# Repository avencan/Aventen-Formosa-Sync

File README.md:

<div align="center">

> ## ⚠️ This board has been superseded
> **Aventen Formosa Sync** has been replaced by the **[Aventen Kypros](https://github.com/avencan/Aventen-Kypros)** — a completely redesigned board with WiFi 6, HDMI output, Gigabit Ethernet, native Zigbee/Thread/Matter, on-board audio codec, and 2× the compute power.
>
> 👉 **[See the Kypros → github.com/avencan/Aventen-Kypros](https://github.com/avencan/Aventen-Kypros)**
> 👉 **[Join the waitlist → aventeninnovations.com](https://aventeninnovations.com/#waitlist)**

</div>

---

<div align="center">

# Aventen Formosa Sync

### The board that started it all.

</div>

---

## Introduction

The Aventen Formosa Sync was Aventen's first development board — a high-performance board equipped with a 600MHz RT1060 MCU (overclockable to 1GHz under the right conditions), built-in WiFi 5 + Bluetooth with audio, USB OTG, RGB LEDs, USB-C connectivity, and comprehensive battery management.

Designed for IoT makers, professionals, and industrial solutions — it offered a compact, breadboardable form factor with serious performance.

---

## Specs

| Feature | Detail |
|---|---|
| **MCU** | NXP MIMXRT106SDVL6B — ARM Cortex-M7 @ 600MHz (overclockable to 1GHz) |
| **PSRAM** | 8MB |
| **Flash** | 16MB |
| **WiFi** | WiFi 5 — Murata Type 1ZM |
| **Bluetooth** | BT 5.0 |
| **SD Card** | Built-in MicroSD slot |
| **USB** | USB-C |
| **Ethernet** | 10/100 via LAN8720A |
| **LEDs** | RGB + status LED |
| **GPIO** | 35 header pins |
| **Debug** | SWD/JTAG |
| **Power** | Battery (JST) + USB-C LiPo charging |
| **Extras** | Chip antenna + IPX U.FL · Aux LDO 1A · RF switch |

---

## Add-on Boards

**RJ45 LAN8720A Ethernet Board:**
[github.com/avencan/Aventen-Formosa-Sync/tree/main/RJ45](https://github.com/avencan/Aventen-Formosa-Sync/tree/main/RJ45)

---

## Status

Formosa Sync reached prototype stage and confirmed first prototype. It was covered by Hackster.io and launched a Crowd Supply campaign. Development was paused in favour of the next-generation Kypros board.

- 📰 [Hackster.io coverage](https://www.hackster.io/news/aventen-formosa-sync-is-a-high-performance-dev-board-running-up-to-1-ghz-f2581d62fd3c)
- 🛒 [Crowd Supply page](https://www.crowdsupply.com/aventen/aventen-formosa-sync)

---

## What Came Next

We built Formosa Sync. Then we asked: *what if we threw out every compromise and started over with the RT1176 — before anyone else did?*

That's **[Kypros](https://github.com/avencan/Aventen-Kypros)**.

| | Formosa Sync | Kypros |
|---|---|---|
| CPU | RT1060 @ 600MHz | **RT1176 @ 1GHz + 400MHz** |
| WiFi | WiFi 5 | **WiFi 6 (601Mbps)** |
| HDMI | ❌ | **✅ 1080p** |
| Ethernet | 10/100Mbps | **Gigabit** |
| Zigbee/Thread/Matter | ❌ | **✅ Native** |
| Audio Codec | ❌ | **✅ SGTL5000 (98dB SNR)** |
| Ultrasonic Mic | ❌ | **✅ 80kHz** |
| LiPo Native | ✅ | ✅ |
| Form Factor | Breadboardable | **69×18mm** |

👉 **[See the Kypros → github.com/avencan/Aventen-Kypros](https://github.com/avencan/Aventen-Kypros)**

---

<div align="center">

**Built in Britain 🇬🇧 — Loved everywhere.**

*Aventen Innovations Ltd — Eastbourne, UK*

© 2026 Aventen Innovations Ltd · [aventeninnovations.com](https://aventeninnovations.com)

</div>

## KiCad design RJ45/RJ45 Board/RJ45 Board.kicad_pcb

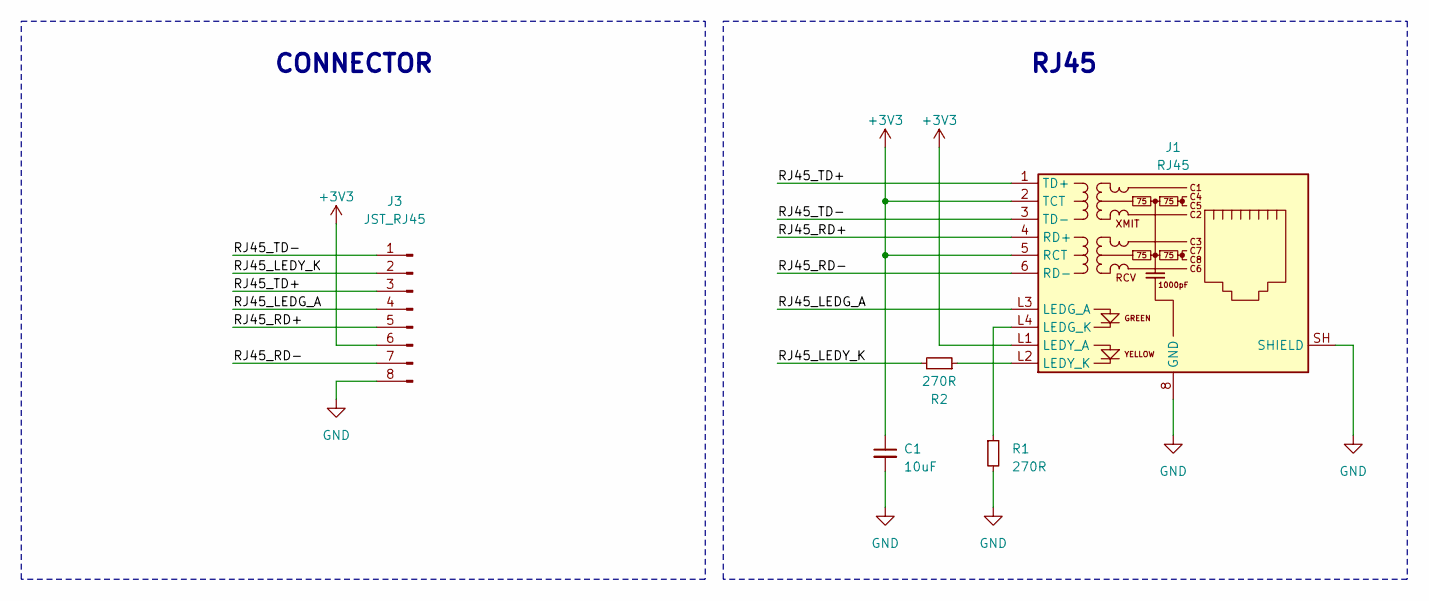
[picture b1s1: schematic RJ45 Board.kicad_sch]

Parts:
C1: 10uF; C_0402_1005Metric; LCSC Part C76991
J1: RJ45; RJ45_Bel_SI-60062-F
J3: JST_RJ45; PinHeader_2x04_P1.27mm_Vertical; LCSC Part C265121
R1, R2: 270R; R_0201_0603Metric; LCSC Part C144821

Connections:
+3V3: C1.1, J1.2 (TCT), J1.5 (RCT), J1.L1 (LEDY_A), J3.6
/RJ45_LEDG_A: J1.L3 (LEDG_A), J3.4
/RJ45_LEDY_K: J3.2, R2.2
/RJ45_RD+: J1.4 (RD+), J3.5
/RJ45_RD-: J1.6 (RD-), J3.7
/RJ45_TD+: J1.1 (TD+), J3.3
/RJ45_TD-: J1.3 (TD-), J3.1
GND: C1.2, J1.8 (GND), J1.SH (SHIELD), J3.8, R1.2
unnamed: J1.L4 (LEDG_K), R1.1
unnamed: J1.L2 (LEDY_K), R2.1

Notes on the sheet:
CONNECTOR
RJ45

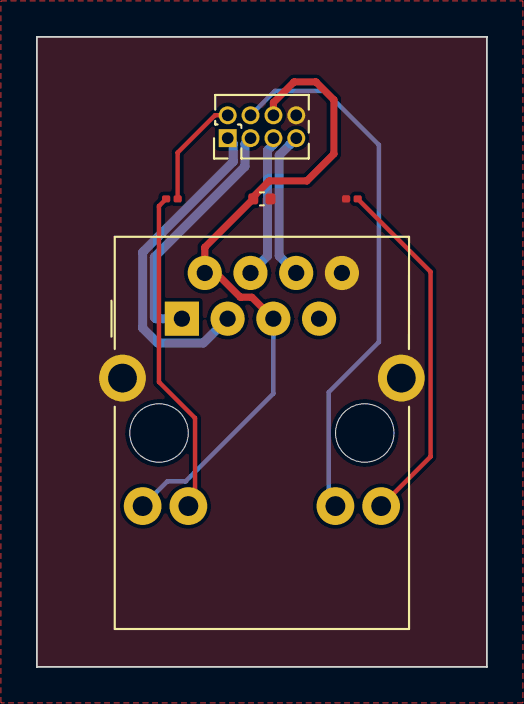
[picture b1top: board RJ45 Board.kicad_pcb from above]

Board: 2 copper layers, 25.0 x 35.0 mm, 5 parts (0 on the bottom side), 10 nets.

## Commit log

2023-10-01 PRE-RELEASE
    Not fully checked, may contain some errors.
2023-12-08 RJ45 Ethernet LAN8720A addon board
2026-05-17 Mark Formosa Sync as superseded by Aventen Kypros
2026-05-17 Update README — superseded notice, Kypros comparison, website links
